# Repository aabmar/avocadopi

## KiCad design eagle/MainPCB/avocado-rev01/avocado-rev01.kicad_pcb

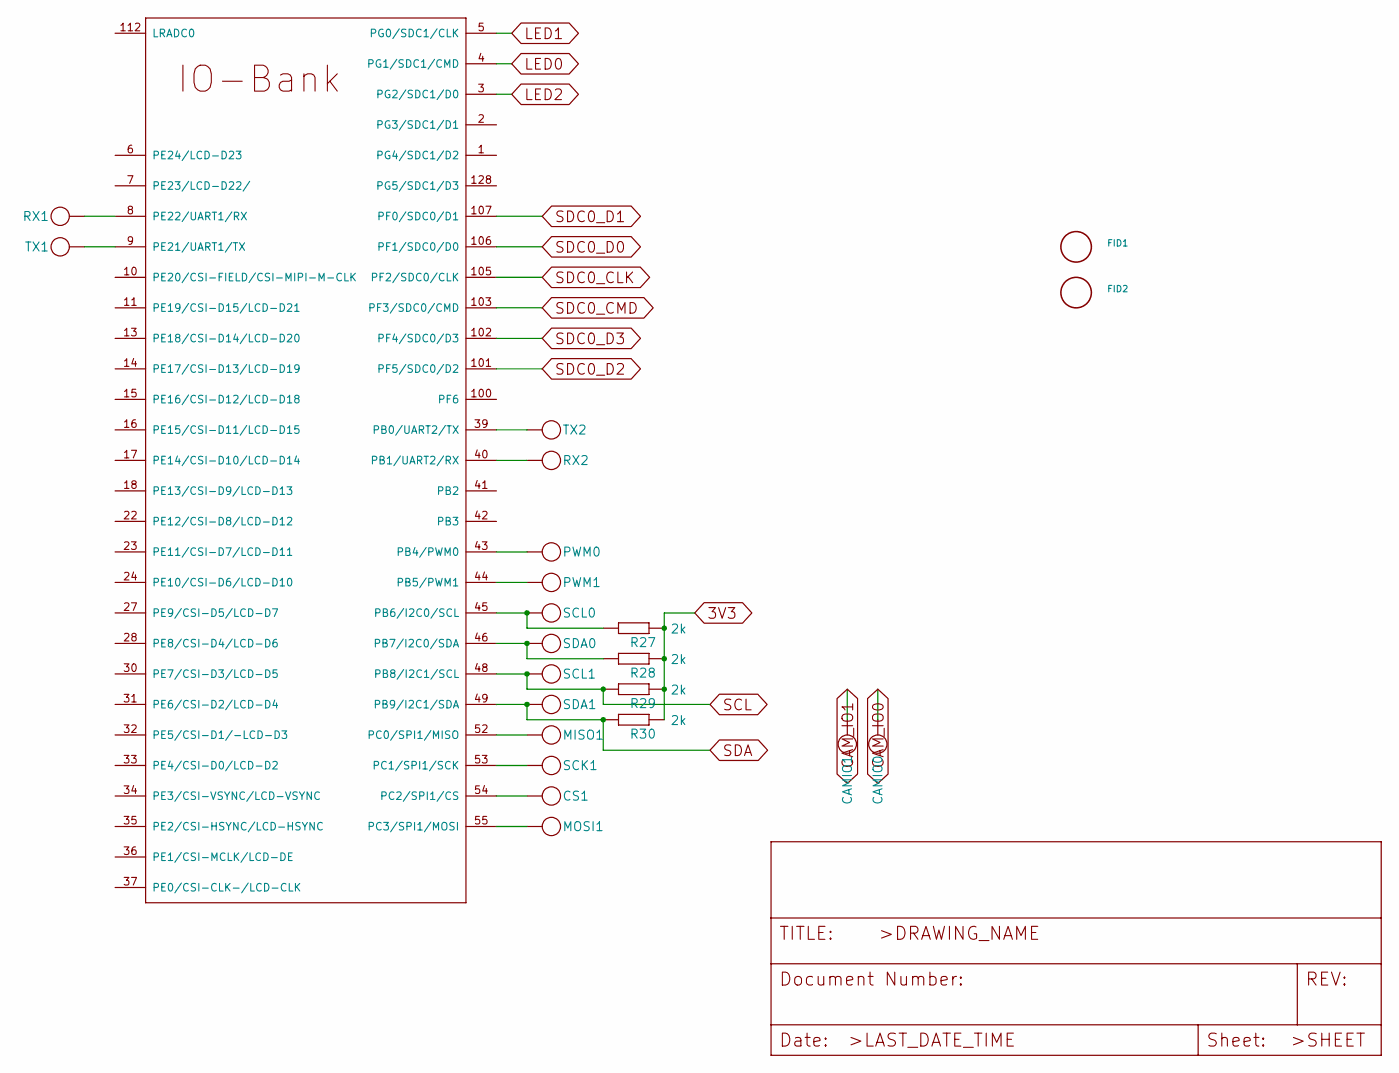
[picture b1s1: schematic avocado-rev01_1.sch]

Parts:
CAMIO0, CAMIO1: TEST_TESTPOINT
CS: TEST_TESTPOINT
FID1, FID2: FIDUCIAL; FIDUCIAL_1MM
MISO: TEST_TESTPOINT
MOSI: TEST_TESTPOINT
PWM0, PWM1: TEST_TESTPOINT
R27, R28, R29, R30: 2k; R0603
RX1, RX2: TEST_TESTPOINT
SCK: TEST_TESTPOINT
SCL0, SCL1: TEST_TESTPOINT
SDA0, SDA1: TEST_TESTPOINT
TX1, TX2: TEST_TESTPOINT
U1: V3S; QFP-128

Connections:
3V3: R27.1, R28.1, R29.1, R30.1; also elsewhere on the board
CAM_IO0: CAMIO0.1; also elsewhere on the board
CAM_IO1: CAMIO1.1; also elsewhere on the board
LED0: U1.4 (PG1/SDC1/CMD); also elsewhere on the board
LED1: U1.5 (PG0/SDC1/CLK); also elsewhere on the board
LED2: U1.3 (PG2/SDC1/D0); also elsewhere on the board
unnamed 30: U1.54 (PC2/SPI1/CS); also elsewhere on the board
unnamed 38: U1.52 (PC0/SPI1/MISO); also elsewhere on the board
unnamed 39: U1.55 (PC3/SPI1/MOSI); also elsewhere on the board
unnamed: PWM0.1, U1.43 (PB4/PWM0)
unnamed: PWM1.1, U1.44 (PB5/PWM1)
unnamed: R27.2, SCL0.1, U1.45 (PB6/I2C0/SCL)
unnamed: R28.2, SDA0.1, U1.46 (PB7/I2C0/SDA)
unnamed: RX1.1, U1.8 (PE22/UART1/RX)
unnamed: RX2.1, U1.40 (PB1/UART2/RX)
unnamed 56: U1.53 (PC1/SPI1/SCK); also elsewhere on the board
unnamed: TX1.1, U1.9 (PE21/UART1/TX)
unnamed: TX2.1, U1.39 (PB0/UART2/TX)
SCL: R29.2, SCL1.1, U1.48 (PB8/I2C1/SCL); also elsewhere on the board
SDA: R30.2, SDA1.1, U1.49 (PB9/I2C1/SDA); also elsewhere on the board
SDC0_CLK: U1.105 (PF2/SDC0/CLK); also elsewhere on the board
SDC0_CMD: U1.103 (PF3/SDC0/CMD); also elsewhere on the board
SDC0_D0: U1.106 (PF1/SDC0/D0); also elsewhere on the board
SDC0_D1: U1.107 (PF0/SDC0/D1); also elsewhere on the board
SDC0_D2: U1.101 (PF5/SDC0/D2); also elsewhere on the board
SDC0_D3: U1.102 (PF4/SDC0/D3); also elsewhere on the board

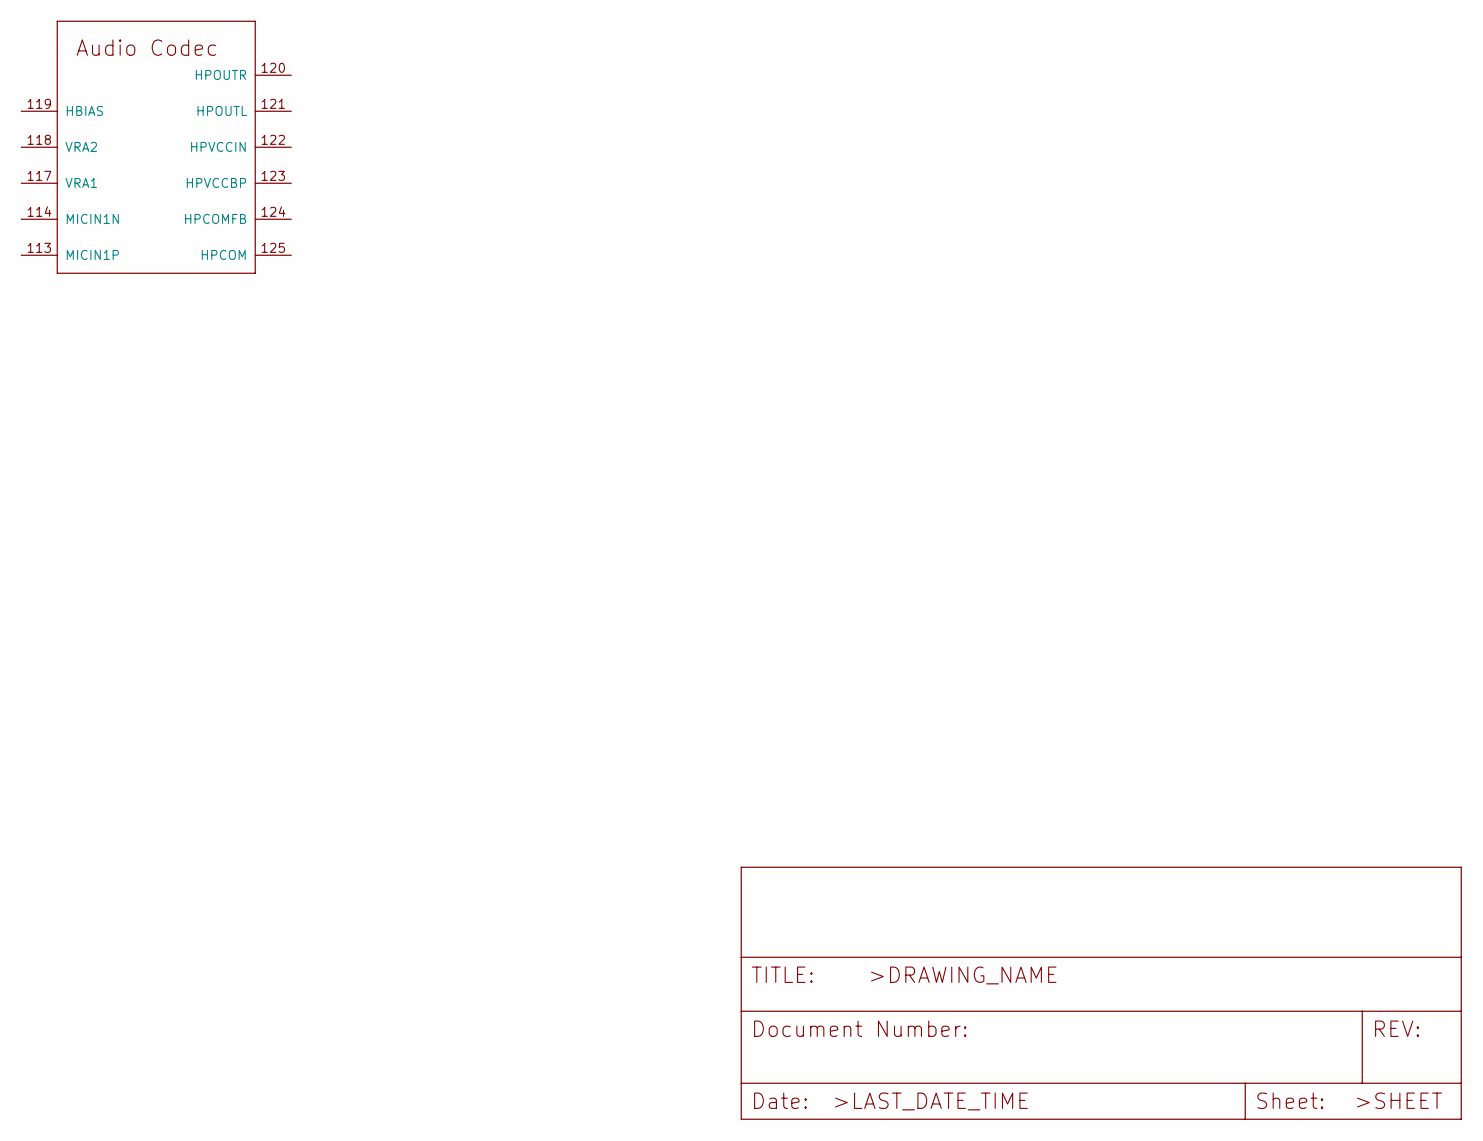
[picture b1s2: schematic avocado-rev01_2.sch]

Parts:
U1: V3S; QFP-128

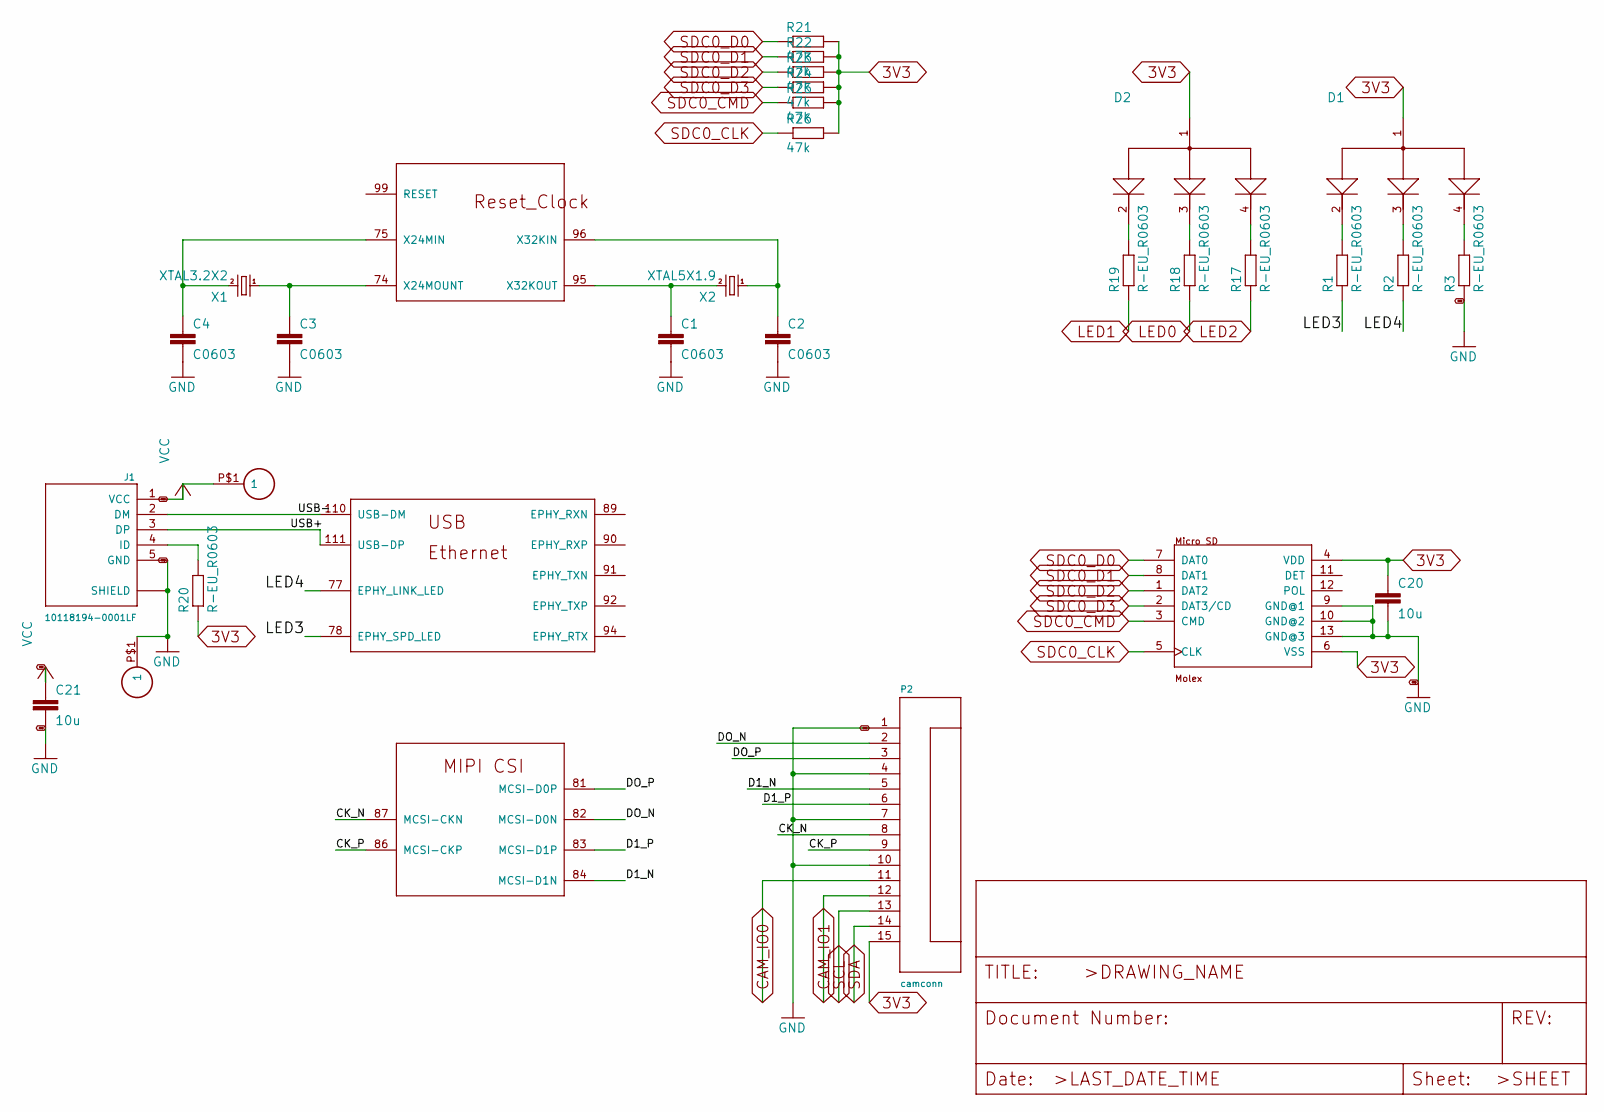
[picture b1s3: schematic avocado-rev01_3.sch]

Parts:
5V: PADTH; PAD
C1, C2, C3, C4: C0603
C20, C21: 10u; C0603
D1, D2: LL-R3528RGBC-008-B; LED_LL-R3528RGBC-008-B
GND: PADTH; PAD
J1: 10118194-0001LF; AMPHENOL_10118194-0001LF
J3: 0475710001; MOLEX_0475710001
P2: camconn; 686115148922
R1, R2, R3, R17, R18, R19, R20: R-EU_R0603; R0603
R21, R22, R23, R24, R25, R26: 47k; R0603
U1: V3S; QFP-128
X1: XTAL3.2X2; 3.2X2-4
X2: XTAL5X1.9; XTAL-5X1.9

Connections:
3V3: C20.1, D1.1 (COMM_ANODE), D2.1 (COMM_ANODE), J3.4 (VDD), J3.6 (VSS), P2.15, R20.1, R21.2, R22.2, R23.2, R24.2, R25.2, R26.2; also elsewhere on the board
/avocado-rev01_3/CK_N: P2.8, U1.87 (MCSI-CKN)
/avocado-rev01_3/CK_P: P2.9, U1.86 (MCSI-CKP)
/avocado-rev01_3/D1_N: P2.5 (D1_N), U1.84 (MCSI-D1N)
/avocado-rev01_3/D1_P: P2.6 (D1_P), U1.83 (MCSI-D1P)
/avocado-rev01_3/DO_N: P2.2 (DO_N), U1.82 (MCSI-D0N)
/avocado-rev01_3/DO_P: P2.3 (DO_P), U1.81 (MCSI-D0P)
/avocado-rev01_3/LED3: R1.1, U1.78 (EPHY_SPD_LED)
/avocado-rev01_3/LED4: R2.1, U1.77 (EPHY_LINK_LED)
/avocado-rev01_3/USB+: J1.3 (DP), U1.111 (USB-DP)
/avocado-rev01_3/USB-: J1.2 (DM), U1.110 (USB-DM)
CAM_IO0: P2.11; also elsewhere on the board
CAM_IO1: P2.12; also elsewhere on the board
GND: C1.2, C2.2, C3.2, C4.2, C20.2, C21.2, J1.5 (GND), J1.S1 (SHIELD), J1.S2 (SHIELD), J1.S3 (SHIELD), J1.S4 (SHIELD), J1.S5 (SHIELD), J1.S6 (SHIELD), J3.9 (GND@1), J3.10 (GND@2), J3.13 (GND@3), P2.1, P2.4, P2.7, P2.10, R3.1; also elsewhere on the board
LED0: R18.1; also elsewhere on the board
LED1: R19.1; also elsewhere on the board
LED2: R17.1; also elsewhere on the board
unnamed: C1.1, U1.95 (X32KOUT), X2.P$2 (2)
unnamed: C2.1, U1.96 (X32KIN), X2.P$1 (1)
unnamed: C3.1, U1.74 (X24MOUNT), X1.P$1 (1)
unnamed: C4.1, U1.75 (X24MIN), X1.P$3 (2)
unnamed: D1.2 (CATHODE_RED), R1.2
unnamed: D1.3 (CATHODE_GREEN), R2.2
unnamed: D1.4 (CATHODE_BLUE), R3.2
unnamed: D2.2 (CATHODE_RED), R19.2
unnamed: D2.3 (CATHODE_GREEN), R18.2
unnamed: D2.4 (CATHODE_BLUE), R17.2
unnamed: J1.4 (ID), R20.2
SCL: P2.13; also elsewhere on the board
SDA: P2.14; also elsewhere on the board
SDC0_CLK: J3.5 (CLK), R26.1; also elsewhere on the board
SDC0_CMD: J3.3 (CMD), R25.1; also elsewhere on the board
SDC0_D0: J3.7 (DAT0), R21.1; also elsewhere on the board
SDC0_D1: J3.8 (DAT1), R22.1; also elsewhere on the board
SDC0_D2: J3.1 (DAT2), R23.1; also elsewhere on the board
SDC0_D3: J3.2 (DAT3/CD), R24.1; also elsewhere on the board
VCC: C21.1, J1.1 (VCC); also elsewhere on the board

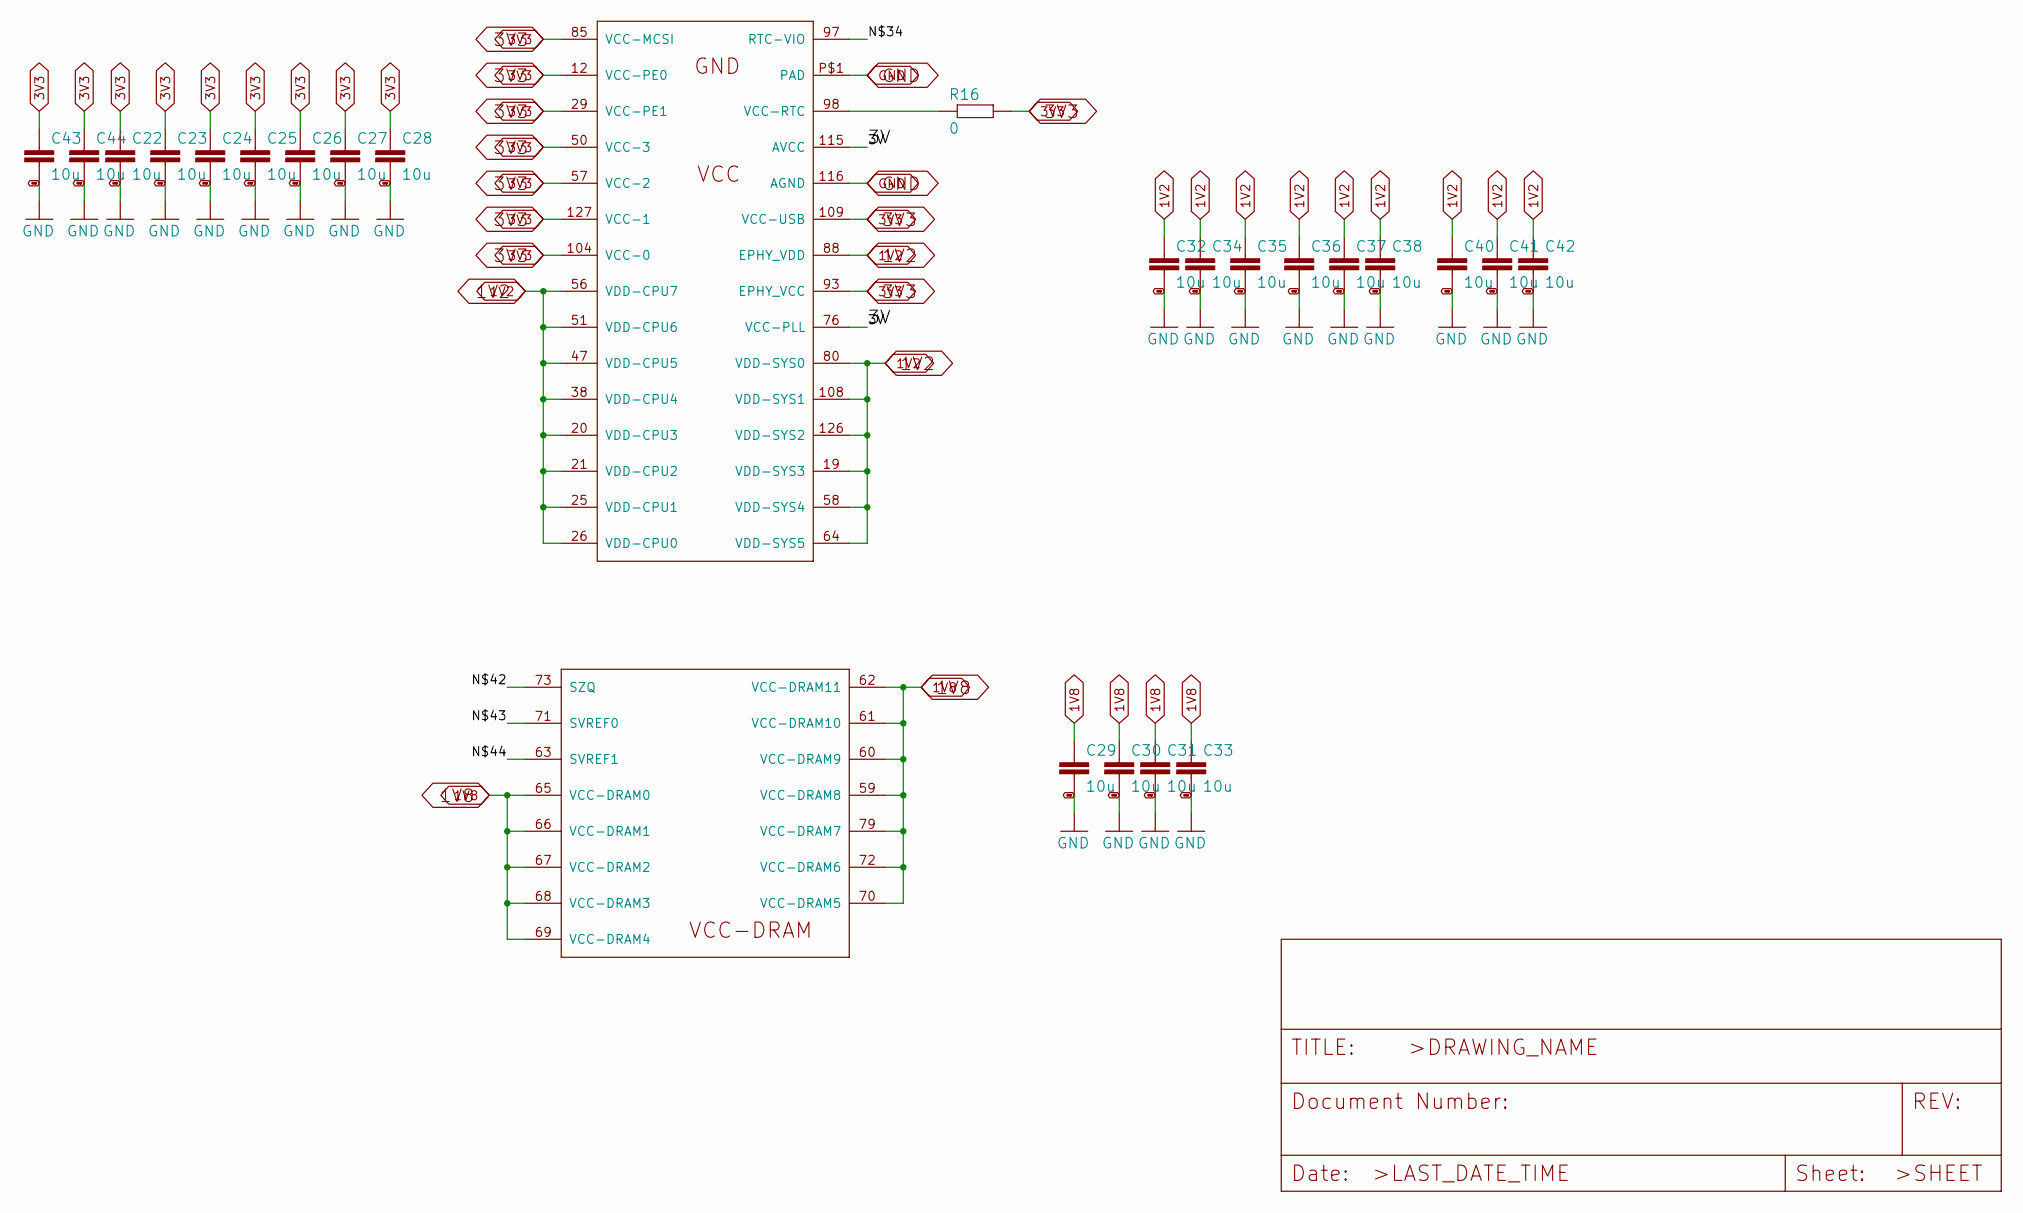
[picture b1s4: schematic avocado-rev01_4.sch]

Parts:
C22, C23, C24, C25, C26, C27, C28, C29, C30, C31, C32, C33, C34, C35, C36, C37, C38, C40, C41, C42, C43, C44: 10u; C0603
R16: 0; R0603
U1: V3S; QFP-128

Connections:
1V2: C32.1, C34.1, C35.1, C36.1, C37.1, C38.1, C40.1, C41.1, C42.1, U1.19 (VDD-SYS3), U1.20 (VDD-CPU3), U1.21 (VDD-CPU2), U1.25 (VDD-CPU1), U1.26 (VDD-CPU0), U1.38 (VDD-CPU4), U1.47 (VDD-CPU5), U1.51 (VDD-CPU6), U1.56 (VDD-CPU7), U1.58 (VDD-SYS4), U1.64 (VDD-SYS5), U1.80 (VDD-SYS0), U1.88 (EPHY_VDD), U1.108 (VDD-SYS1), U1.126 (VDD-SYS2); also elsewhere on the board
1V8: C29.1, C30.1, C31.1, C33.1, U1.59 (VCC-DRAM8), U1.60 (VCC-DRAM9), U1.61 (VCC-DRAM10), U1.62 (VCC-DRAM11), U1.65 (VCC-DRAM0), U1.66 (VCC-DRAM1), U1.67 (VCC-DRAM2), U1.68 (VCC-DRAM3), U1.69 (VCC-DRAM4), U1.70 (VCC-DRAM5), U1.72 (VCC-DRAM6), U1.79 (VCC-DRAM7); also elsewhere on the board
3V: U1.76 (VCC-PLL), U1.115 (AVCC); also elsewhere on the board
3V3: C22.1, C23.1, C24.1, C25.1, C26.1, C27.1, C28.1, C43.1, C44.1, R16.2, U1.12 (VCC-PE0), U1.29 (VCC-PE1), U1.50 (VCC-3), U1.57 (VCC-2), U1.85 (VCC-MCSI), U1.93 (EPHY_VCC), U1.104 (VCC-0), U1.109 (VCC-USB), U1.127 (VCC-1); also elsewhere on the board
GND: C22.2, C23.2, C24.2, C25.2, C26.2, C27.2, C28.2, C29.2, C30.2, C31.2, C32.2, C33.2, C34.2, C35.2, C36.2, C37.2, C38.2, C40.2, C41.2, C42.2, C43.2, C44.2, U1.116 (AGND), U1.P$1 (PAD); also elsewhere on the board
unnamed: R16.1, U1.98 (VCC-RTC)

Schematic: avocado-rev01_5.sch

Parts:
C5, C10, C15: 1u; C0603
C6, C9, C11, C14, C16, C19: 100n; C0603
C7, C8, C12, C13, C17, C18: 22u; CAP4.3X6.1
C39, C45: 10u; C0603
L1, L2, L3: CALC; B82462A4153K
R4, R8, R12: 100k; R0603
R5, R9, R13: 59k; R0603
R6, R7, R10, R11, R14, R15: CALC; R0603
U2, U3, U4: AP65111A; TSOT26
U5: XC6206P302MR; SOT-23

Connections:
1V2: C18.1 (+), C19.1, L3.P$2 (2), R14.1; also elsewhere on the board
1V8: C13.1 (+), C14.1, L2.P$2 (2), R10.1; also elsewhere on the board
3V: C39.1, C45.1, U5.2; also elsewhere on the board
3V3: C8.1 (+), C9.1, L1.P$2 (2), R6.1, U5.3; also elsewhere on the board
GND: C6.2, C7.2 (-), C8.2 (-), C9.2, C11.2, C12.2 (-), C13.2 (-), C14.2, C16.2, C17.2 (-), C18.2 (-), C19.2, C39.2, C45.2, R7.2, R11.2, R15.2, U2.2 (GND), U3.2 (GND), U4.2 (GND), U5.1; also elsewhere on the board
unnamed: C5.1, U2.4 (BST)
unnamed: C5.2, L1.P$1 (1), U2.3 (SW)
unnamed: C10.1, U3.4 (BST)
unnamed: C10.2, L2.P$1 (1), U3.3 (SW)
unnamed: C15.1, U4.4 (BST)
unnamed: C15.2, L3.P$1 (1), U4.3 (SW)
unnamed: R4.1, U2.5 (ENABLE)
unnamed: R5.1, R6.2, R7.1
unnamed: R5.2, U2.6 (FB)
unnamed: R8.1, U3.5 (ENABLE)
unnamed: R9.2, U3.6 (FB)
unnamed: R9.1, R10.2, R11.1
unnamed: R12.1, U4.5 (ENABLE)
unnamed: R13.1, R14.2, R15.1
unnamed: R13.2, U4.6 (FB)
VCC: C6.1, C7.1 (+), C11.1, C12.1 (+), C16.1, C17.1 (+), R4.2, R8.2, R12.2, U2.1 (VIN), U3.1 (VIN), U4.1 (VIN); also elsewhere on the board

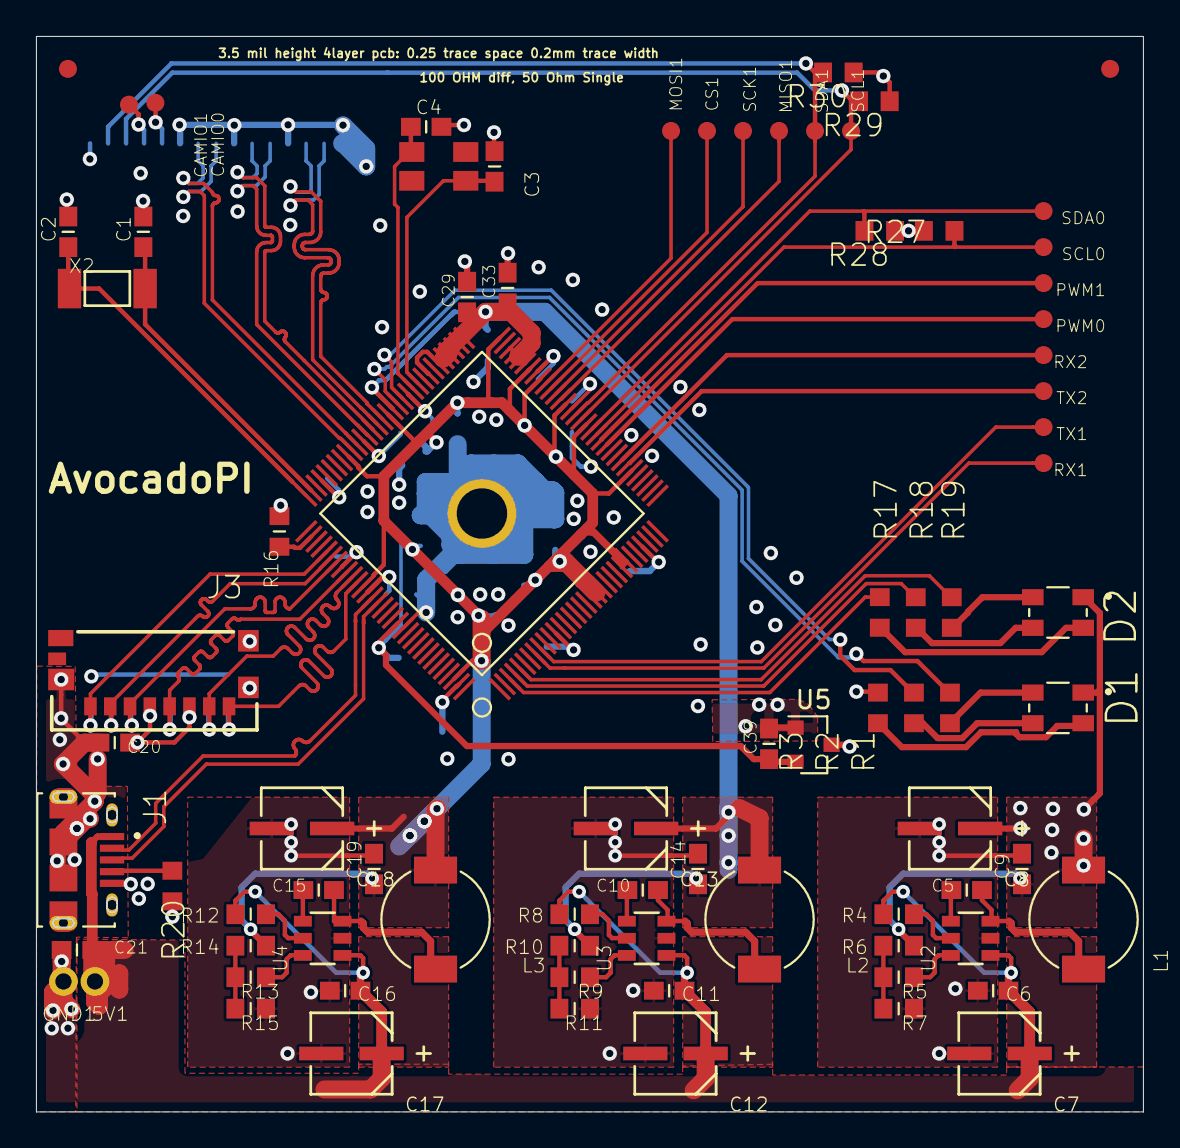
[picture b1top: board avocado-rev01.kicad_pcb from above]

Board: 4 copper layers, 61.5 x 59.8 mm, 110 parts (0 on the bottom side), 68 nets.

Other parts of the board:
5V1: PADTH; PAD
CS1: TEST_TESTPOINT
GND1: PADTH; PAD
MISO1: TEST_TESTPOINT
MOSI1: TEST_TESTPOINT
SCK1: TEST_TESTPOINT

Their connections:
GND: GND1.P$1; also elsewhere on the board
unnamed 30: CS1.1; also elsewhere on the board
unnamed 38: MISO1.1; also elsewhere on the board
unnamed 39: MOSI1.1; also elsewhere on the board
unnamed 56: SCK1.1; also elsewhere on the board
VCC: 5V1.P$1; also elsewhere on the board

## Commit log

2019-02-23 Set up Schematics with V3s
2019-02-28 updated schematic
2019-02-28 Connected power
2019-02-28 Removed backup files
2019-03-01 connected sd card and added led
2019-03-01 added testpoints
2019-03-01 updated i2c
2019-03-04 connected psu in schem
2019-03-04 placement
2019-03-04 shitty routing v1
2019-03-06 accurate high speed routing, now 4 layer
2019-03-06 better routing v2
2019-03-06 better routing v3
2019-03-08 decoupling caps
2019-03-11 added 3V rail
2019-03-18 updated decoupling vias
2019-03-19 update keepout area
2019-03-21 add axp209
2019-03-21 updated values
2019-03-25 added jumpers
2019-03-25 high
2019-03-26 Added design rules
2019-03-26 working
2019-03-27 In progress
2019-04-11 Added gfx
2019-04-11 Changed usb connector
2019-04-13 Added server example, and a partial C implementation
2019-04-13 Added some gcode example files
2019-04-13 C and Python implementation for gcode analisys
2019-04-25 Added pin header for RX0/TX0
2019-04-25 Fixed some labels.
2019-04-25 CAM job
2019-04-27 added usb lib
2019-05-04 Changed 0402 to 0603, adjusted some line
